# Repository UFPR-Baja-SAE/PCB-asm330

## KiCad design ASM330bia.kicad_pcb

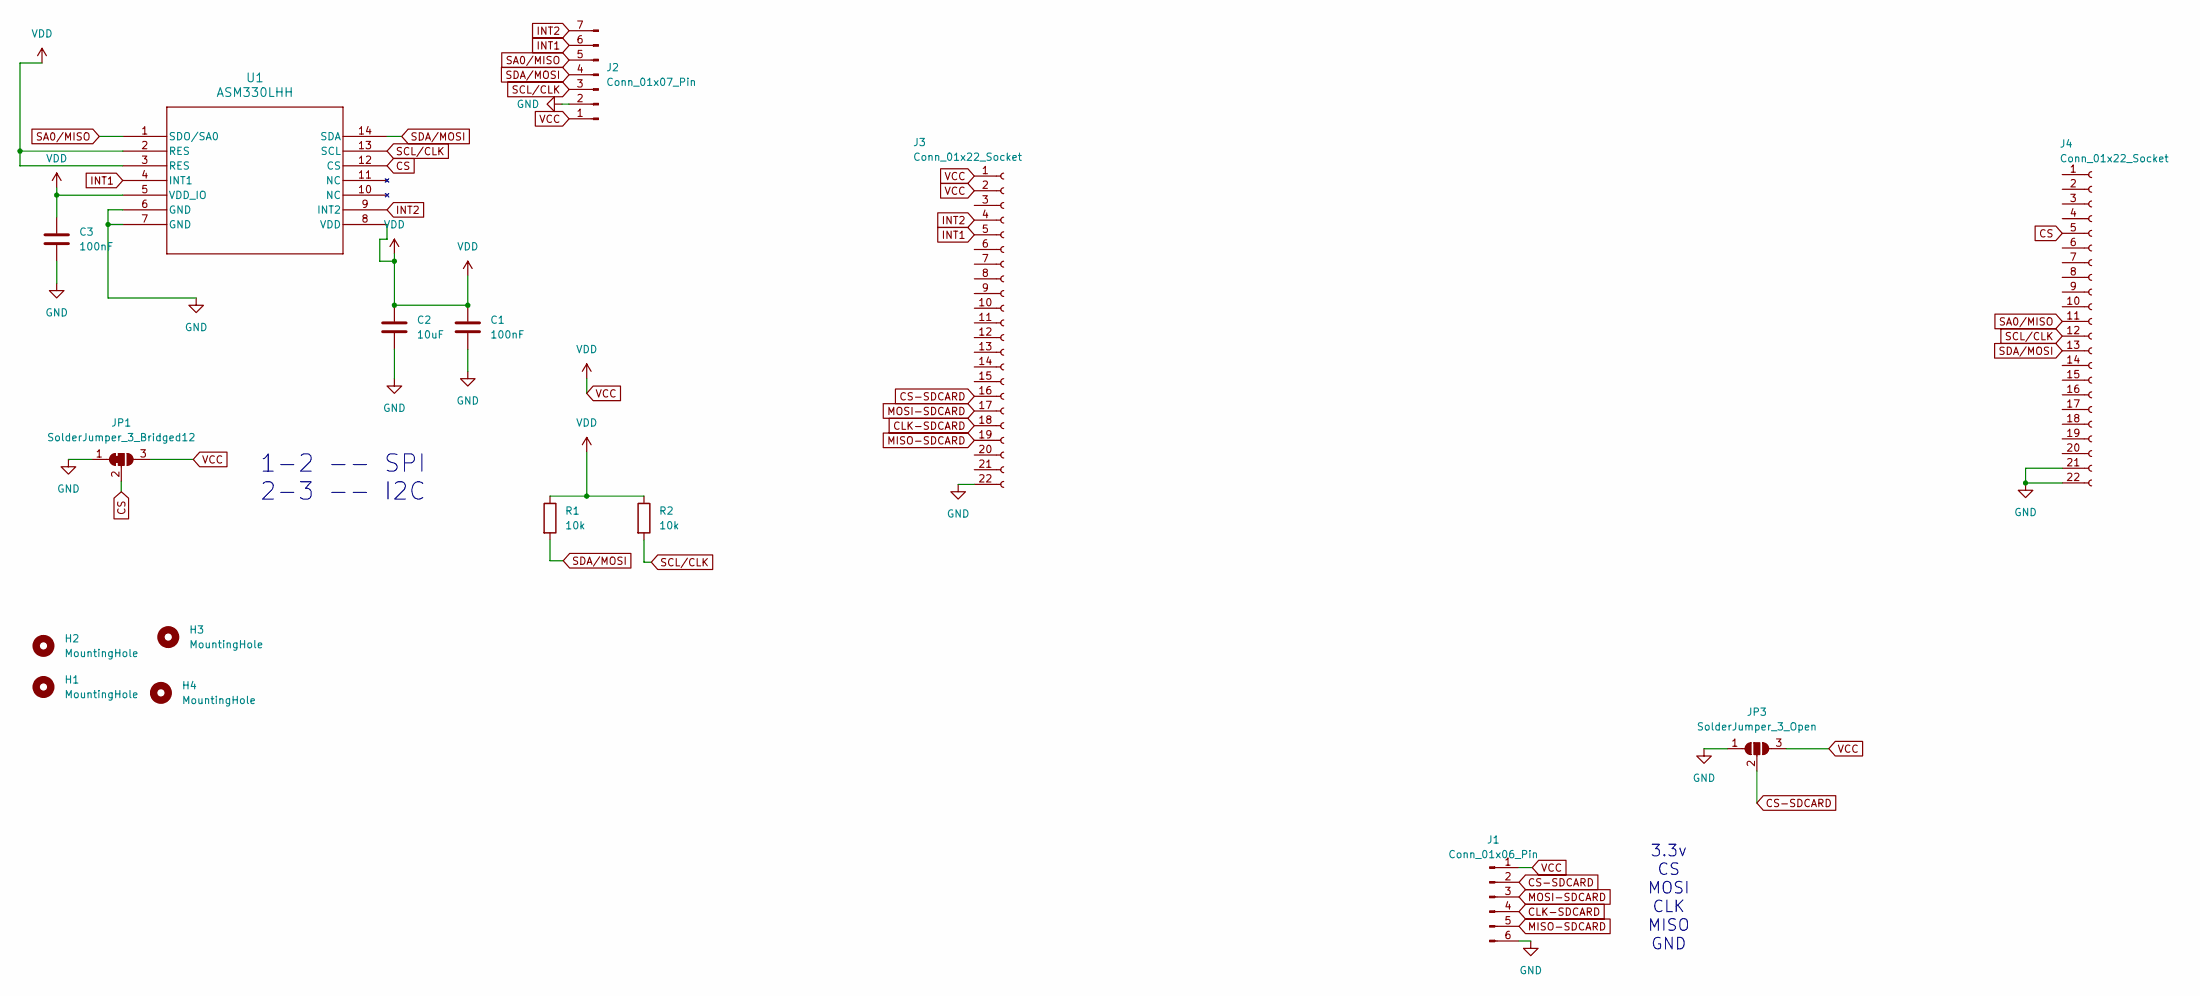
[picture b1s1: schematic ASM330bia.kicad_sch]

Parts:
C1, C3: 100nF; C_0603_1608Metric
C2: 10uF; C_0603_1608Metric
H1, H2, H3, H4: MountingHole; MountingHole_2.7mm
J1: Conn_01x06_Pin; PinHeader_1x06_P2.54mm_Vertical
J2: Conn_01x07_Pin; PinSocket_1x07_P2.54mm_Vertical
J3, J4: Conn_01x22_Socket; PinHeader_1x22_P2.54mm_Vertical
JP1: SolderJumper_3_Bridged12; SolderJumper-3_P1.3mm_Bridged12_RoundedPad1.0x1.5mm
JP3: SolderJumper_3_Open; SolderJumper-3_P1.3mm_Open_RoundedPad1.0x1.5mm
R1, R2: 10k; C_0603_1608Metric
U1: ASM330LHH; LGA-14L_2P5X3X0P83_STM

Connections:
CLK-SDCARD: J1.4, J3.18
CS: J4.5, JP1.2 (C), U1.12 (CS)
CS-SDCARD: J1.2, J3.16, JP3.2 (C)
GND: C1.2, C2.2, C3.2, J1.6, J2.2, J3.22, J4.21, J4.22, JP1.1 (A), JP3.1 (A), U1.6 (GND), U1.7 (GND)
INT1: J2.6, J3.5, U1.4 (INT1)
INT2: J2.7, J3.4, U1.9 (INT2)
MISO-SDCARD: J1.5, J3.19
MOSI-SDCARD: J1.3, J3.17
SA0/MISO: J2.5, J4.11, U1.1 (SDO/SA0)
SCL/CLK: J2.3, J4.12, R2.2, U1.13 (SCL)
SDA/MOSI: J2.4, J4.13, R1.2, U1.14 (SDA)
VCC: C1.1, C2.1, C3.1, J1.1, J2.1, J3.1, J3.2, JP1.3 (B), JP3.3 (B), R1.1, R2.1, U1.2 (RES), U1.3 (RES), U1.5 (VDD_IO), U1.8 (VDD)

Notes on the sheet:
3.3v CS MOSI CLK MISO GND
1-2 -- SPI 2-3 -- I2C

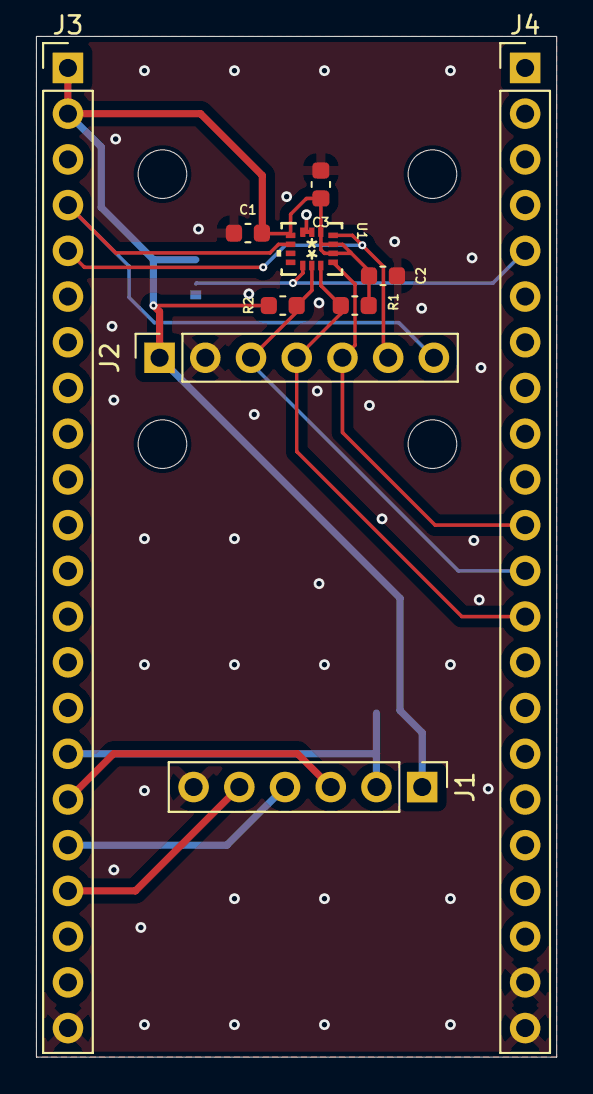
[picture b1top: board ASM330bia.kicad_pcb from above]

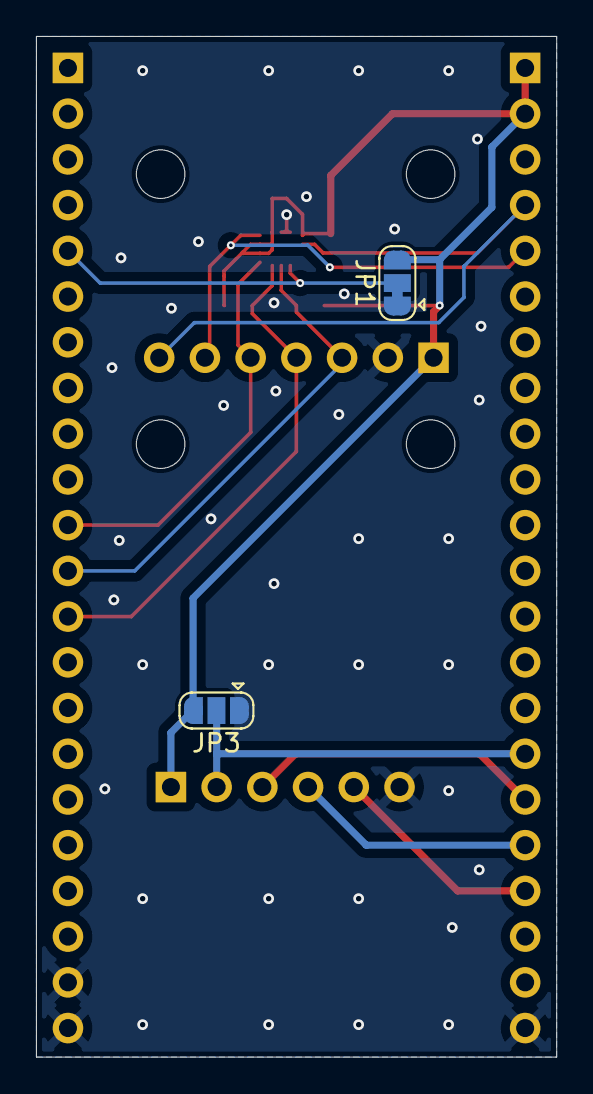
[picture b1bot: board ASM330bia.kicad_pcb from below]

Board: 2 copper layers, 28.9 x 56.7 mm, 16 parts (2 on the bottom side), 12 nets.

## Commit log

2024-09-10 PCB asm330
2025-01-11 alteração do furo passante
2025-08-31 Att
    Adicionado interrupts e revisado design pcb e alimentação
2026-01-16 Adição ESP32-S3 e modulo SDCARD
